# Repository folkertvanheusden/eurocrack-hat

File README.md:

For more info, see https://nurdspace.nl/Nurdspace_eurorack_raspberry_pi_hat

Currently (2022/7/14) this project is far from finished. The pcb published is not even tested.

Comments welcome!

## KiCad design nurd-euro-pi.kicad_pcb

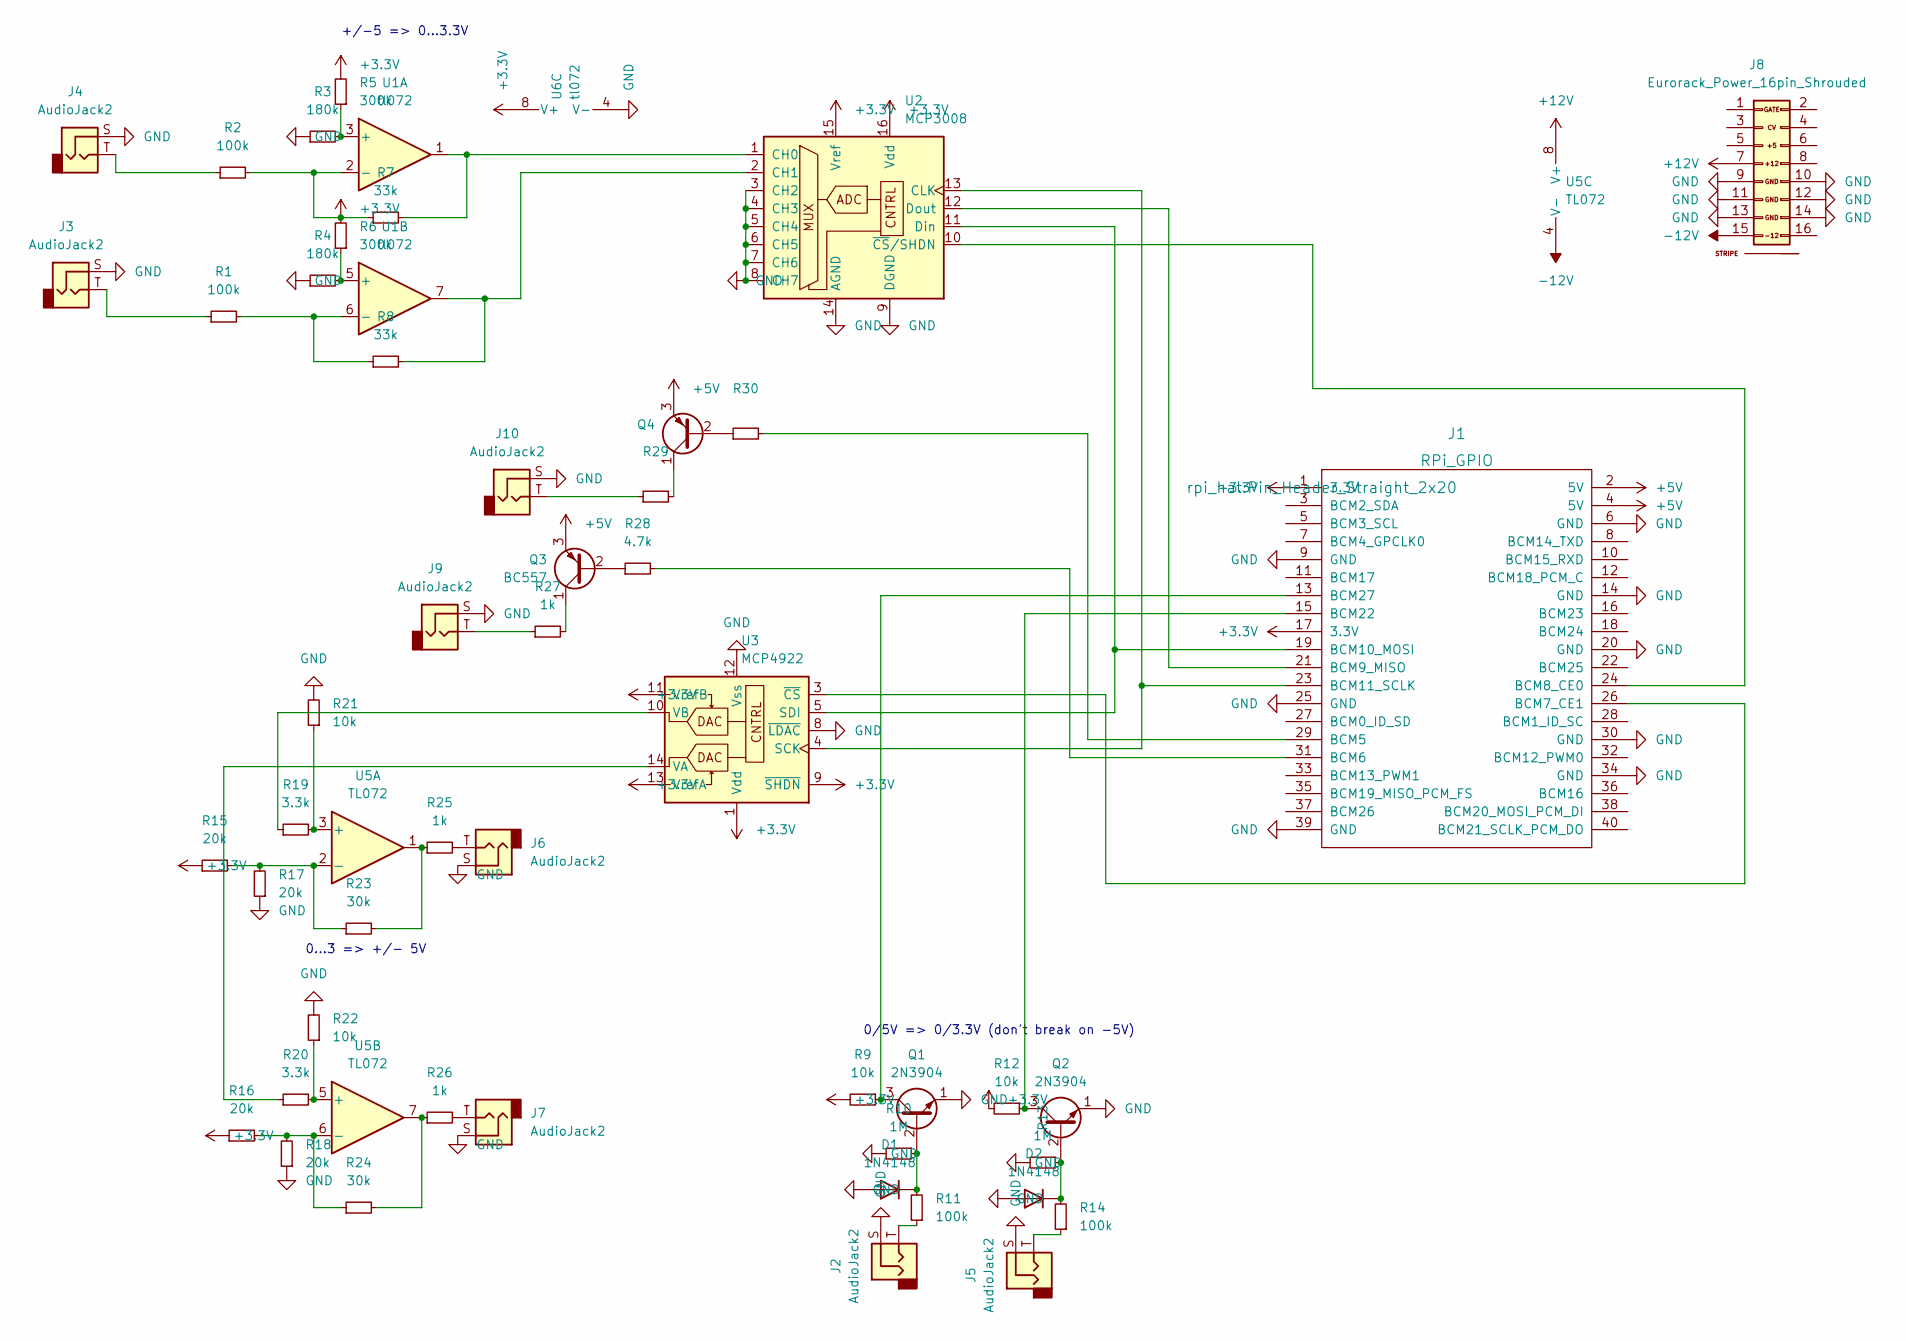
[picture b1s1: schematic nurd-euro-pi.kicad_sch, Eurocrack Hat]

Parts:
D1, D2: 1N4148; D_DO-35_SOD27_P7.62mm_Horizontal
J1: RPi_GPIO; Pin_Header_Straight_2x20
J2, J3, J4, J5, J6, J7, J9, J10: AudioJack2; Jack_3.5mm_QingPu_WQP-PJ398SM_Vertical_CircularHoles
J8: Eurorack_Power_16pin_Shrouded; Pins_2x08_2.54mm_TH_EuroPower_Shrouded; Part Number LL1007-1 (2*8 HITEMP)
Q1, Q2: 2N3904; TO-92_Inline
Q3: BC557; TO-92_Inline
Q4: (no value)
R1, R2, R11, R14: 100k; R_Axial_DIN0207_L6.3mm_D2.5mm_P7.62mm_Horizontal
R3, R4: 180k; R_Axial_DIN0207_L6.3mm_D2.5mm_P7.62mm_Horizontal
R5, R6: 300k; R_Axial_DIN0207_L6.3mm_D2.5mm_P7.62mm_Horizontal
R7, R8: 33k; R_Axial_DIN0207_L6.3mm_D2.5mm_P7.62mm_Horizontal
R9, R12, R21, R22: 10k; R_Axial_DIN0207_L6.3mm_D2.5mm_P7.62mm_Horizontal
R10, R13: 1M; R_Axial_DIN0207_L6.3mm_D2.5mm_P7.62mm_Horizontal
R15, R16, R17, R18: 20k; R_Axial_DIN0207_L6.3mm_D2.5mm_P7.62mm_Horizontal
R19, R20: 3.3k; R_Axial_DIN0207_L6.3mm_D2.5mm_P7.62mm_Horizontal
R23, R24: 30k; R_Axial_DIN0207_L6.3mm_D2.5mm_P7.62mm_Horizontal
R25, R26, R27: 1k; R_Axial_DIN0207_L6.3mm_D2.5mm_P7.62mm_Horizontal
R28: 4.7k; R_Axial_DIN0207_L6.3mm_D2.5mm_P7.62mm_Horizontal
R29, R30: (no value)
U1, U6: tl072; DIP-8_W7.62mm_Socket_LongPads
U2: MCP3008; DIP-16_W7.62mm_Socket_LongPads
U3: MCP4922; DIP-14_W7.62mm_Socket_LongPads
U5: TL072; DIP-8_W7.62mm_Socket_LongPads

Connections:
+3V3: J1.1 (3.3V), J1.17 (3.3V), R2.2, R5.2, R6.2, R7.1, R9.2, R12.2, R15.1, R16.1, U1.2 (-), U2.15 (Vref), U2.16 (Vdd), U3.1 (Vdd), U3.9 (~SHDN), U3.11 (VrefB), U3.13 (VrefA), U6.8 (V+)
+5V: J1.2 (5V), J1.4 (5V), Q3.3 (E), Q4.3 (E)
+12V: J8.7 (12V), U5.8 (V+)
-12V: J8.15 (-12V), U5.4 (V-)
GND: D1.2 (A), D2.2 (A), J1.6 (GND), J1.9 (GND), J1.14 (GND), J1.20 (GND), J1.25 (GND), J1.30 (GND), J1.34 (GND), J1.39 (GND), J2.S, J3.S, J4.S, J5.S, J6.S, J7.S, J8.9 (GND), J8.10 (GND), J8.11 (GND), J8.12 (GND), J8.13 (-12), J8.14 (-12V), J9.S, J10.S, Q1.1 (E), Q2.1 (E), R3.1, R4.1, R10.2, R13.2, R17.1, R18.1, R21.2, R22.2, U2.3 (CH2), U2.4 (CH3), U2.5 (CH4), U2.6 (CH5), U2.7 (CH6), U2.8 (CH7), U2.9 (DGND), U2.14 (AGND), U3.8 (~LDAC), U3.12 (Vss), U6.4 (V-)
unnamed: D1.1 (K), Q1.2 (B), R10.1, R11.2
unnamed: D2.1 (K), Q2.2 (B), R13.1, R14.2
unnamed: J1.13 (BCM27), Q1.3 (C), R9.1
unnamed: J1.15 (BCM22), Q2.3 (C), R12.1
unnamed: J1.19 (BCM10_MOSI), U2.11 (Din), U3.5 (SDI)
unnamed: J1.21 (BCM9_MISO), U2.12 (Dout)
unnamed: J1.23 (BCM11_SCLK), U2.13 (CLK), U3.4 (SCK)
unnamed: J1.24 (BCM8_CE0), U2.10 (~CS/SHDN)
unnamed: J1.26 (BCM7_CE1), U3.3 (~CS)
unnamed: J1.29 (BCM5), R30.2
unnamed: J1.31 (BCM6), R28.2
unnamed: J2.T, R11.1
unnamed: J3.T, R1.1
unnamed: J4.T, R2.1
unnamed: J5.T, R14.1
unnamed: J6.T, R25.2
unnamed: J7.T, R26.2
unnamed: J9.T, R27.1
unnamed: J10.T, R29.1
unnamed: Q3.1 (C), R27.2
unnamed: Q3.2 (B), R28.1
unnamed: Q4.1 (C), R29.2
unnamed: Q4.2 (B), R30.1
unnamed: R1.2, R8.1, U1.6 (-)
unnamed: R3.2, R5.1, U1.3 (+)
unnamed: R4.2, R6.1, U1.5 (+)
unnamed: R7.2, U1.1, U2.1 (CH0)
unnamed: R8.2, U1.7, U2.2 (CH1)
unnamed: R15.2, R17.2, R23.1, U5.2 (-)
unnamed: R16.2, R18.2, R24.1, U5.6 (-)
unnamed: R19.1, U3.10 (VB)
unnamed: R19.2, R21.1, U5.3 (+)
unnamed: R20.1, U3.14 (VA)
unnamed: R20.2, R22.1, U5.5 (+)
unnamed: R23.2, R25.1, U5.1
unnamed: R24.2, R26.1, U5.7

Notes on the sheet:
0...3 => +/- 5V
0/5V => 0/3.3V (don't break on -5V)
+/-5 => 0...3.3V

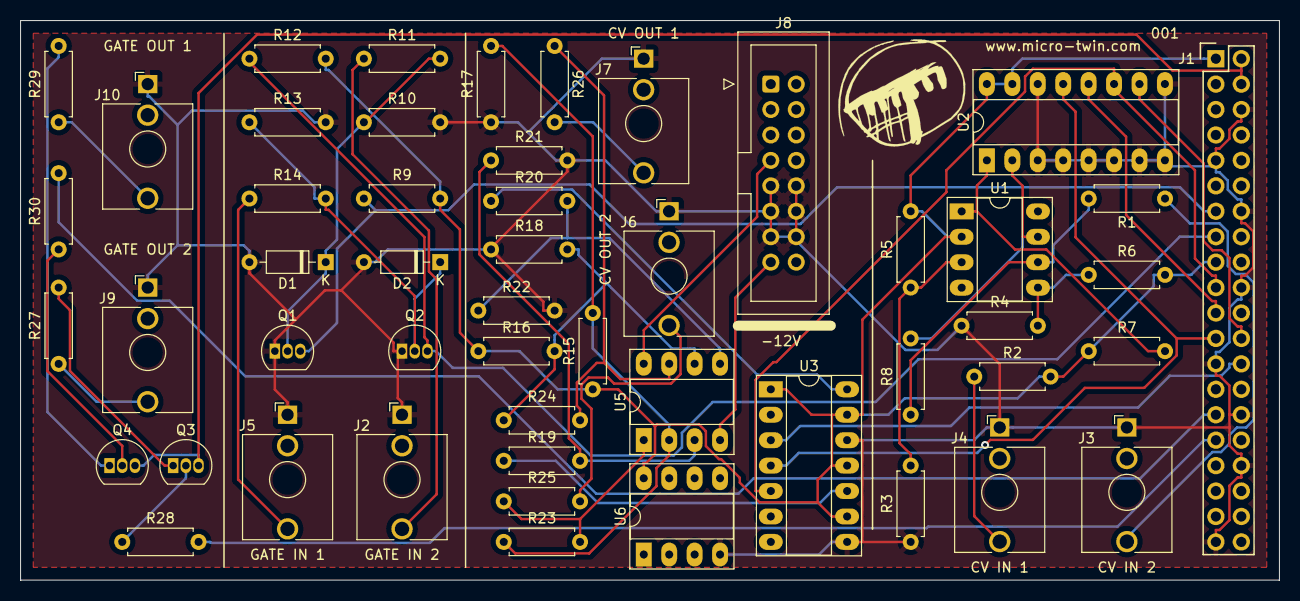
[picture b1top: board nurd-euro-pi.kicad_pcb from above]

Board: 2 copper layers, 125.7 x 55.9 mm, 51 parts (0 on the bottom side), 41 nets.

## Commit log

2022-07-14 1st commit
2022-07-15 descriptions
2022-07-28 Added gate-out
